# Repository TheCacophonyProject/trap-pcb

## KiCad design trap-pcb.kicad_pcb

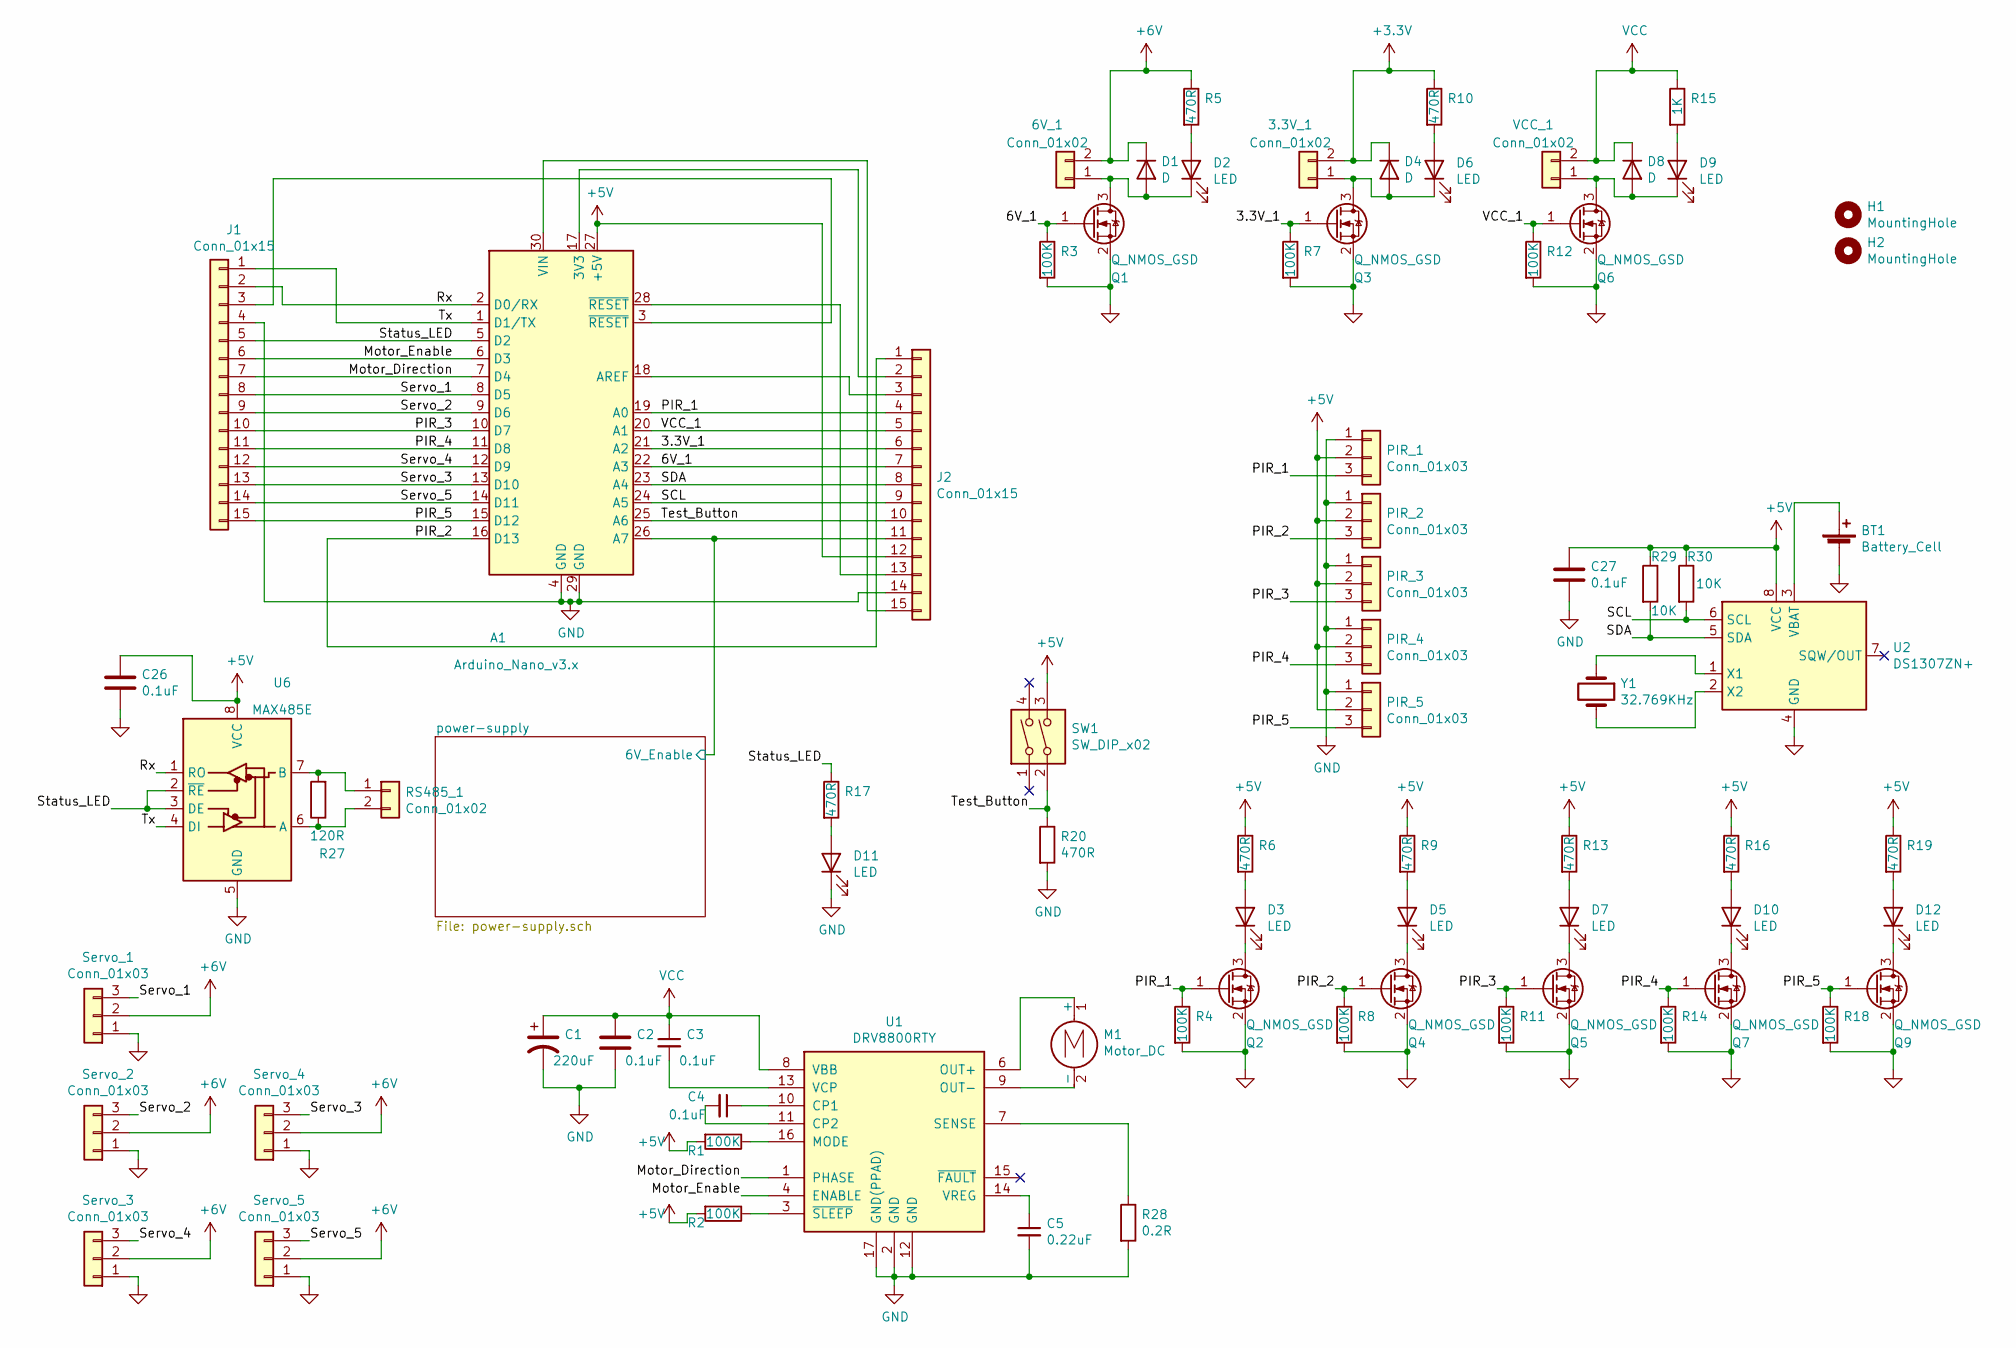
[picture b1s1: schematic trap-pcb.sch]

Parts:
3.3V_1, 6V_1: Conn_01x02; JST_XH_B2B-XH-A_1x02_P2.50mm_Vertical
A1: Arduino_Nano_v3.x; Arduino_Nano
BT1: Battery_Cell; BatteryHolder_Keystone_1060_1x2032; JLCPCB SMD C70377
C1: 220uF; CP_Elec_8x10; JLCPCB SMD C134765
C2, C3, C4, C26: 0.1uF; C_0603_1608Metric; JLCPCB SMD C14663
C5: 0.22uF; C_0603_1608Metric; JLCPCB SMD C21120
C27: 0.1uF; C_0603_1608Metric; JLCPCB SMD C134765
D1, D4, D8: D; D_SMA; JLCPCB SMD C95872
D2, D3, D5, D6, D7, D9, D10, D11, D12: LED; LED_0603_1608Metric; JLCPCB SMD C2286
H1, H2: MountingHole; MountingHole_4.3mm_M4
J1, J2: Conn_01x15; PinHeader_1x15_P2.54mm_Vertical
M1: Motor_DC; JST_XH_B2B-XH-A_1x02_P2.50mm_Vertical
PIR_1, PIR_2, PIR_3, PIR_4, PIR_5: Conn_01x03; JST_XH_B3B-XH-A_1x03_P2.50mm_Vertical
Q1, Q2, Q3, Q4, Q5, Q6, Q7, Q9: Q_NMOS_GSD; SOT-23; JLCPCB SMD C20917
R1, R2, R3, R4, R7, R8, R11, R12, R14, R18: 100K; R_0603_1608Metric; JLCPCB SMD C25803
R5, R6, R9, R10, R13, R16, R17, R19, R20: 470R; R_0603_1608Metric; JLCPCB SMD C23179
R15: 1K; R_0603_1608Metric; JLCPCB SMD C21190
R27: 120R; R_0603_1608Metric; JLCPCB SMD C22787
R28: 0.2R; R_2512_6332Metric; JLCPCB SMD C76258
R29, R30: 10K; R_0603_1608Metric; JLCPCB SMD C39050
RS485_1: Conn_01x02; JST_XH_B2B-XH-A_1x02_P2.50mm_Vertical
SW1: SW_DIP_x02; Push_E-Switch_KS01Q01
Servo_1, Servo_2, Servo_3, Servo_4, Servo_5: Conn_01x03; JST_XH_B3B-XH-A_1x03_P2.50mm_Vertical
U1: DRV8800RTY; Texas_S-PWQFN-N16_EP2.1x2.1mm_ThermalVias; JLCPCB SMD C330401
U2: DS1307ZN+; SOIC-8_3.9x4.9mm_P1.27mm; JLCPCB SMD C26858
U6: MAX485E; SOIC-8_3.9x4.9mm_P1.27mm; JLCPCB SMD C23492
VCC_1: Conn_01x02; JST_XH_B2B-XH-A_1x02_P2.50mm_Vertical
Y1: 32.769KHz; Crystal_SMD_3215-2Pin_3.2x1.5mm; JLCPCB SMD C32346

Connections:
+3V3: 3.3V_1.2, D4.1 (K), R10.1; also elsewhere on the board
+5V: A1.27 (+5V), C26.1, C27.1, J2.12, PIR_1.2, PIR_2.2, PIR_3.2, PIR_4.2, PIR_5.2, R1.2, R2.2, R6.1, R9.1, R13.1, R16.1, R19.1, R29.1, R30.1, SW1.3, U2.8 (VCC), U6.8 (VCC); also elsewhere on the board
+6V: 6V_1.2, D1.1 (K), R5.1, Servo_1.2, Servo_2.2, Servo_3.2, Servo_4.2, Servo_5.2; also elsewhere on the board
/3.3V_1: A1.21 (A2), J2.6, Q3.1 (G), R7.1
/6V_1: A1.22 (A3), J2.7, Q1.1 (G), R3.1
/Motor_Direction: A1.7 (D4), J1.7, U1.1 (PHASE)
/Motor_Enable: A1.6 (D3), J1.6, U1.4 (ENABLE)
/PIR_1: A1.19 (A0), J2.4, PIR_1.3, Q2.1 (G), R4.1
/PIR_2: A1.16 (D13), J2.1, PIR_2.3, Q4.1 (G), R8.1
/PIR_3: A1.10 (D7), J1.10, PIR_3.3, Q5.1 (G), R11.1
/PIR_4: A1.11 (D8), J1.11, PIR_4.3, Q7.1 (G), R14.1
/PIR_5: A1.15 (D12), J1.15, PIR_5.3, Q9.1 (G), R18.1
/Rx: A1.2 (D0/RX), J1.2, U6.1 (RO)
/SCL: A1.24 (A5), J2.9, R30.2, U2.6 (SCL)
/SDA: A1.23 (A4), J2.8, R29.2, U2.5 (SDA)
/Servo_1: A1.8 (D5), J1.8, Servo_1.3
/Servo_2: A1.9 (D6), J1.9, Servo_2.3
/Servo_3: A1.13 (D10), J1.13, Servo_4.3
/Servo_4: A1.12 (D9), J1.12, Servo_3.3
/Servo_5: A1.14 (D11), J1.14, Servo_5.3
/Status_LED: A1.5 (D2), J1.5, R17.1, U6.2 (~RE), U6.3 (DE)
/Test_Button: A1.25 (A6), J2.10, R20.1, SW1.2
/Tx: A1.1 (D1/TX), J1.1, U6.4 (DI)
/VCC_1: A1.20 (A1), J2.5, Q6.1 (G), R12.1
/power-supply/6V_Enable: A1.26 (A7), J2.11; also elsewhere on the board
GND: A1.4 (GND), A1.29 (GND), BT1.2 (-), C1.2, C2.2, C5.2, C26.2, C27.2, D11.1 (K), J1.4, J2.14, PIR_1.1, PIR_2.1, PIR_3.1, PIR_4.1, PIR_5.1, Q1.2 (S), Q2.2 (S), Q3.2 (S), Q4.2 (S), Q5.2 (S), Q6.2 (S), Q7.2 (S), Q9.2 (S), R3.2, R4.2, R7.2, R8.2, R11.2, R12.2, R14.2, R18.2, R20.2, R28.2, Servo_1.1, Servo_2.1, Servo_3.1, Servo_4.1, Servo_5.1, U1.2 (GND), U1.12 (GND), U1.17 (GND(PPAD)), U2.4 (GND), U6.5 (GND); also elsewhere on the board
unnamed: 3.3V_1.1, D4.2 (A), D6.1 (K), Q3.3 (D)
unnamed: 6V_1.1, D1.2 (A), D2.1 (K), Q1.3 (D)
unnamed: A1.3 (~RESET), J1.3
unnamed: A1.17 (3V3), J2.2
unnamed: A1.18 (AREF), J2.3
unnamed: A1.28 (~RESET), J2.13
unnamed: A1.30 (VIN), J2.15
unnamed: BT1.1 (+), U2.3 (VBAT)
unnamed: C3.2, U1.13 (VCP)
unnamed: C4.1, U1.10 (CP1)
unnamed: C4.2, U1.11 (CP2)
unnamed: C5.1, U1.14 (VREG)
unnamed: D2.2 (A), R5.2
unnamed: D3.1 (K), Q2.3 (D)
unnamed: D3.2 (A), R6.2
unnamed: D5.1 (K), Q4.3 (D)
unnamed: D5.2 (A), R9.2
unnamed: D6.2 (A), R10.2
unnamed: D7.1 (K), Q5.3 (D)
unnamed: D7.2 (A), R13.2
unnamed: D8.2 (A), D9.1 (K), Q6.3 (D), VCC_1.1
unnamed: D9.2 (A), R15.2
unnamed: D10.1 (K), Q7.3 (D)
unnamed: D10.2 (A), R16.2
unnamed: D11.2 (A), R17.2
unnamed: D12.1 (K), Q9.3 (D)
unnamed: D12.2 (A), R19.2
unnamed: M1.1 (+), U1.6 (OUT+)
unnamed: M1.2 (-), U1.9 (OUT-)
unnamed: R1.1, U1.16 (MODE)
unnamed: R2.1, U1.3 (~SLEEP)
unnamed: R27.1, RS485_1.2, U6.6 (A)
unnamed: R27.2, RS485_1.1, U6.7 (B)
unnamed: R28.1, U1.7 (SENSE)
unnamed: U2.1 (X1), Y1.1
unnamed: U2.2 (X2), Y1.2
VCC: C1.1, C2.1, C3.1, D8.1 (K), R15.1, U1.8 (VBB), VCC_1.2; also elsewhere on the board

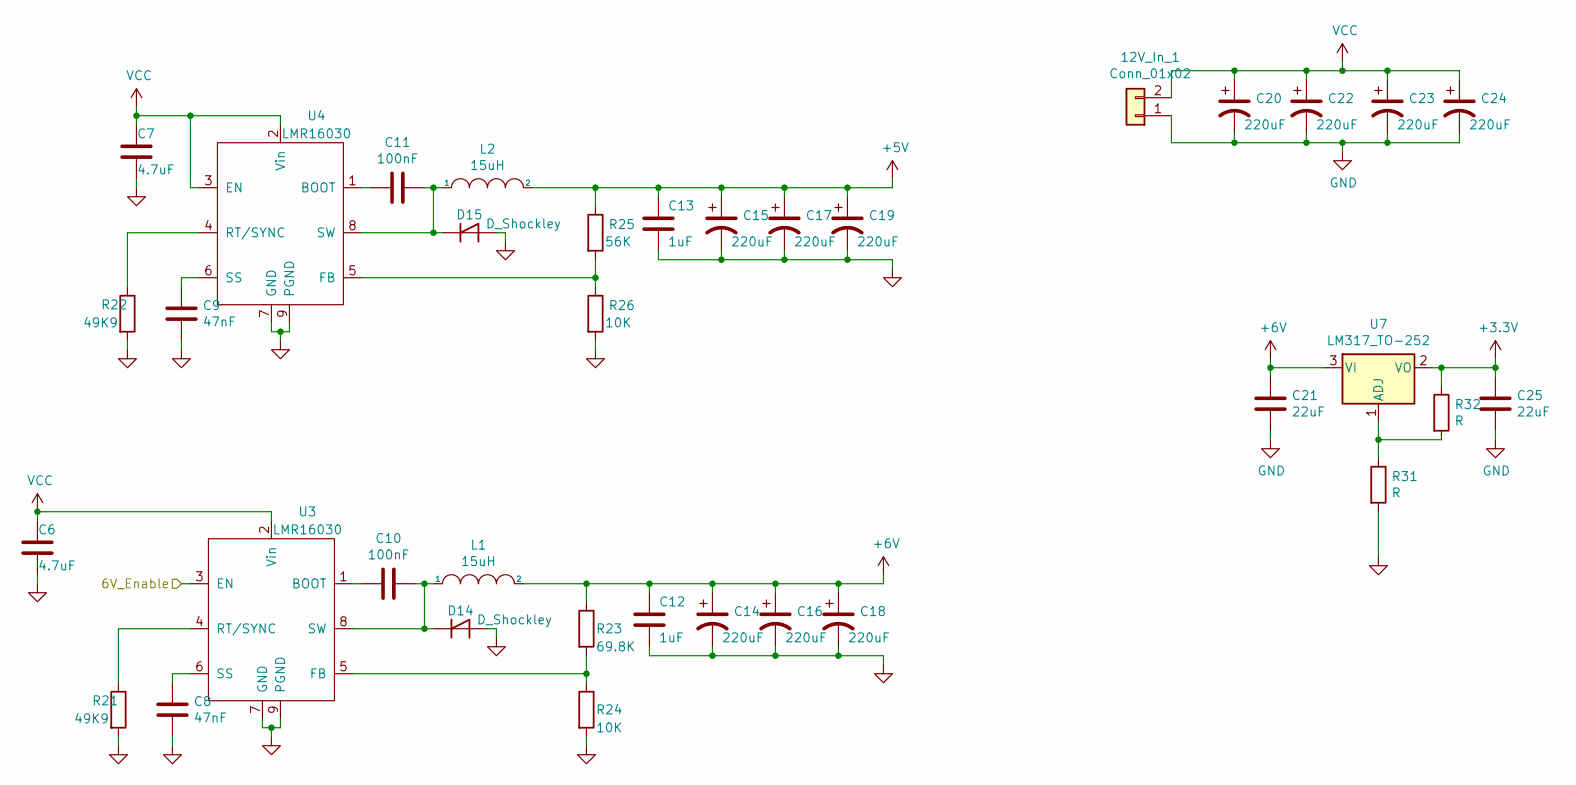
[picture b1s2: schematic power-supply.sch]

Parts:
12V_In_1: Conn_01x02; JST_XH_B2B-XH-A_1x02_P2.50mm_Vertical
C6, C7: 4.7uF; C_0603_1608Metric; JLCPCB SMD C19666
C8, C9: 47nF; C_0603_1608Metric; JLCPCB SMD C1622
C10, C11: 100nF; C_0603_1608Metric; JLCPCB SMD C14663
C12, C13: 1uF; C_0603_1608Metric; JLCPCB SMD C15849
C14, C15, C16, C17, C18, C19, C20, C22, C23, C24: 220uF; CP_Elec_8x10; JLCPCB SMD C134765
C21, C25: 22uF; C_0805_2012Metric; JLCPCB SMD C45783
D14, D15: D_Shockley; D_SMA; JLCPCB SMD C360444
L1, L2: 15uH; MWSA1004; JLCPCB SMD C151872
R21, R22: 49K9; R_0603_1608Metric; JLCPCB SMD C23184
R23: 69.8K; R_0603_1608Metric; JLCPCB SMD C23098
R24, R26: 10K; R_0603_1608Metric; JLCPCB SMD C39050
R25: 56K; R_0603_1608Metric; JLCPCB SMD C351640
R31, R32: R; R_Axial_DIN0309_L9.0mm_D3.2mm_P2.54mm_Vertical
U3, U4: LMR16030; HTSOP-8-1EP_3.9x4.9mm_P1.27mm_EP2.4x3.2mm_ThermalVias; JLCPCB SMD C90665
U7: LM317_TO-252; TO-252-2; JLCPCB SMD C75510

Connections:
+3V3: C25.1, R32.1, U7.2 (VO); also elsewhere on the board
+5V: C13.1, C15.1, C17.1, C19.1, L2.2, R25.1; also elsewhere on the board
+6V: C12.1, C14.1, C16.1, C18.1, C21.1, L1.2, R23.1, U7.3 (VI); also elsewhere on the board
/power-supply/6V_Enable: U3.3 (EN); also elsewhere on the board
GND: 12V_In_1.1, C6.2, C7.2, C8.2, C9.2, C12.2, C13.2, C14.2, C15.2, C16.2, C17.2, C18.2, C19.2, C20.2, C21.2, C22.2, C23.2, C24.2, C25.2, D14.2 (A), D15.2 (A), R21.2, R22.2, R24.2, R26.2, R31.2, U3.7 (GND), U3.9 (PGND), U4.7 (GND), U4.9 (PGND); also elsewhere on the board
unnamed: C8.1, U3.6 (SS)
unnamed: C9.1, U4.6 (SS)
unnamed: C10.1, D14.1 (K), L1.1, U3.8 (SW)
unnamed: C10.2, U3.1 (BOOT)
unnamed: C11.1, D15.1 (K), L2.1, U4.8 (SW)
unnamed: C11.2, U4.1 (BOOT)
unnamed: R21.1, U3.4 (RT/SYNC)
unnamed: R22.1, U4.4 (RT/SYNC)
unnamed: R23.2, R24.1, U3.5 (FB)
unnamed: R25.2, R26.1, U4.5 (FB)
unnamed: R31.1, R32.2, U7.1 (ADJ)
VCC: 12V_In_1.2, C6.1, C7.1, C20.1, C22.1, C23.1, C24.1, U3.2 (Vin), U4.2 (Vin), U4.3 (EN); also elsewhere on the board

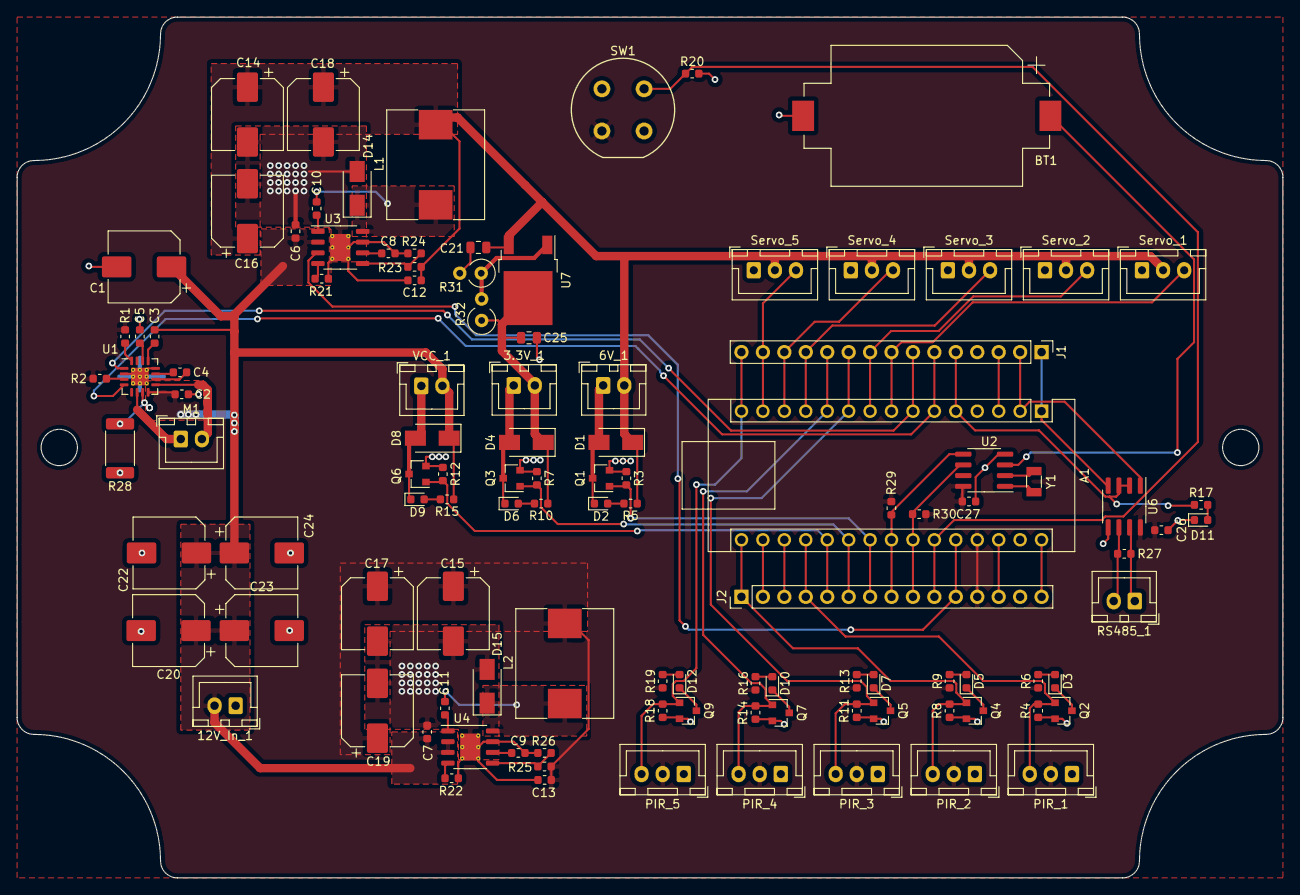
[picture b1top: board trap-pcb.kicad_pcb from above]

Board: 2 copper layers, 150.0 x 102.0 mm, 113 parts (0 on the bottom side), 74 nets.

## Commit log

2020-09-11 Add fabrication folder
2020-09-11 version 0.1.0
2020-09-11 Fix lcsc part number
